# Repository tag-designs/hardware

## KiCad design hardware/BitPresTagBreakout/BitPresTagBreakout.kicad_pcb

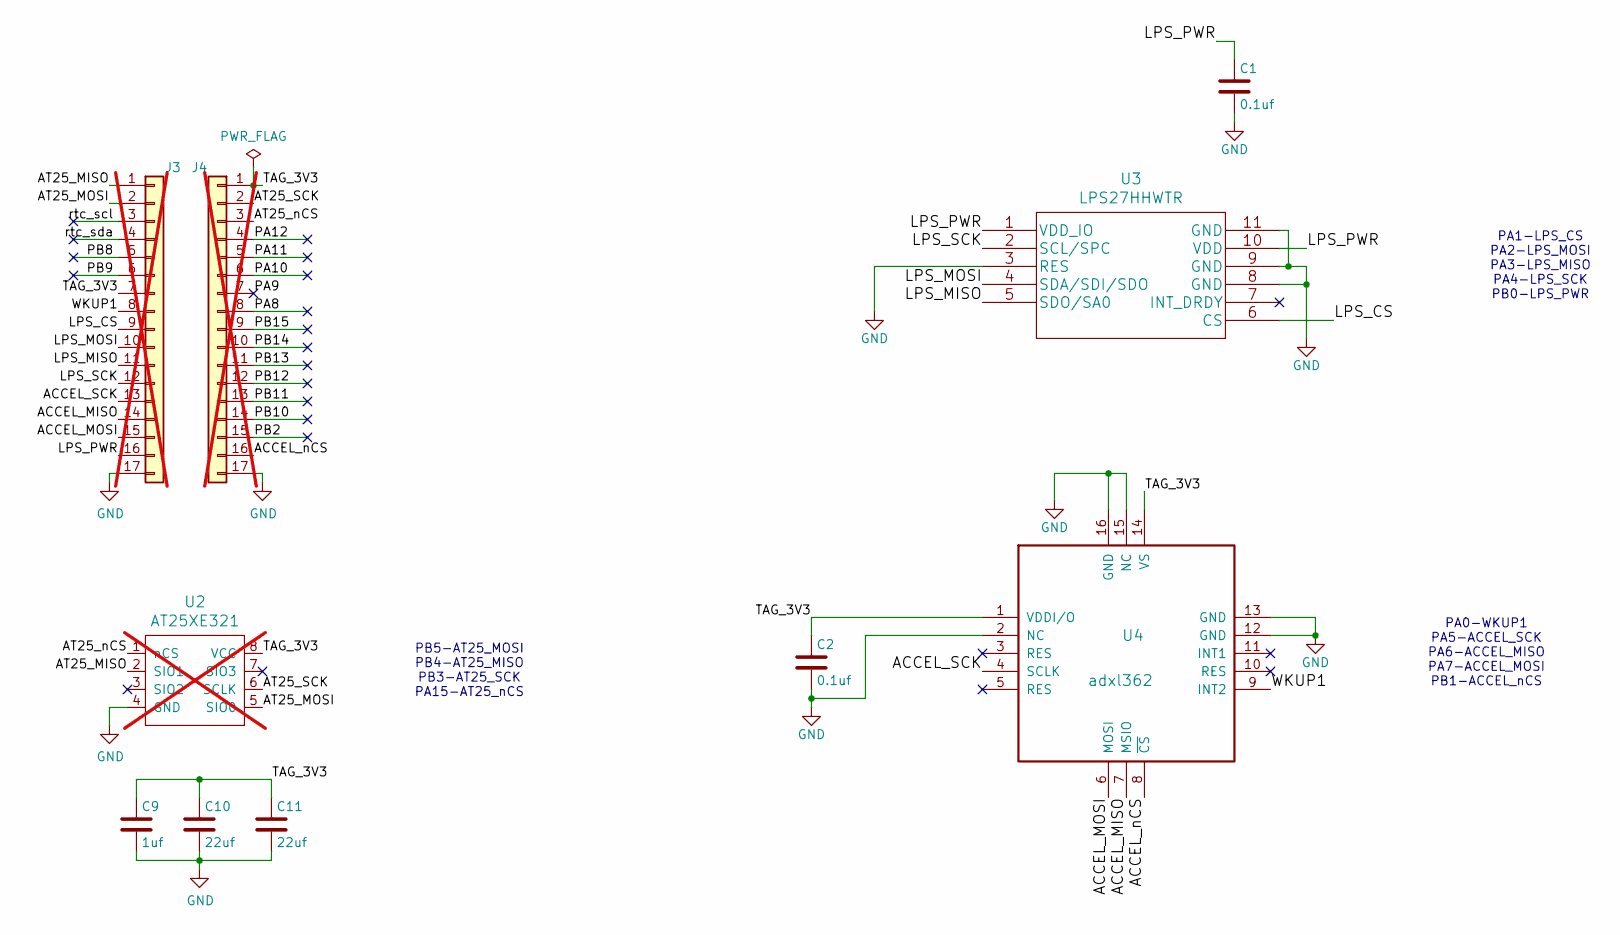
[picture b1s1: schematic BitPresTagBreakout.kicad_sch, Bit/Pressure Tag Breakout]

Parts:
C1, C2: 0.1uf; C_0201_0603Metric; MPN GRM033C81E104KE14D; LCSC C181047
C9: 1uf; C_0201_0603Metric; MPN GRM033R60J105MEA2D; LCSC C76930
C10, C11: 22uf; C_0402_1005Metric; MPN 04026D226MAT2A; LCSC C2179118
J3, J4: Conn_01x17; PinHeader_1x17_P2.54mm_Vertical_Staggered; not fitted
U2: AT25XE321; SO-8_5.3x6.2mm_P1.27mm; MPN AT25XE321D-SSHN-T; LCSC C7455379; not fitted
U3: LPS27HHWTR; MPN LPS27HHTWTR; LCSC C3253631
U4: adxl362; ADXL362; MPN ADXL362BCCZ-RL7; LCSC C192252

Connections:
/ACCEL_MISO: J3.14, U4.7 (MSIO)
/ACCEL_MOSI: J3.15, U4.6 (MOSI)
/ACCEL_SCK: J3.13, U4.4 (SCLK)
/ACCEL_nCS: J4.16, U4.8 (~CS)
/AT25_MISO: J3.1, U2.2 (SIO1)
/AT25_MOSI: J3.2, U2.5 (SIO0)
/AT25_SCK: J4.2, U2.6 (SCLK)
/AT25_nCS: J4.3, U2.1 (nCS)
/LPS_CS: J3.9, U3.6 (CS)
/LPS_MISO: J3.11, U3.5 (SDO/SA0)
/LPS_MOSI: J3.10, U3.4 (SDA/SDI/SDO)
/LPS_PWR: C1.1, J3.16, U3.1 (VDD_IO), U3.10 (VDD)
/LPS_SCK: J3.12, U3.2 (SCL/SPC)
/PA8: J4.8
/PA9: J4.7
/PA10: J4.6
/PA11: J4.5
/PA12: J4.4
/PB2: J4.15
/PB8: J3.5
/PB9: J3.6
/PB10: J4.14
/PB11: J4.13
/PB12: J4.12
/PB13: J4.11
/PB14: J4.10
/PB15: J4.9
/TAG_3V3: C2.1, C9.1, C10.1, C11.1, J3.7, J4.1, U2.8 (VCC), U4.1 (VDDI/O), U4.14 (VS)
/WKUP1: J3.8, U4.9 (INT2)
/rtc_scl: J3.3
/rtc_sda: J3.4
GND: C1.2, C2.2, C9.2, C10.2, C11.2, J3.17, J4.17, U2.4 (GND), U3.3 (RES), U3.8 (GND), U3.9 (GND), U3.11 (GND), U4.2 (NC), U4.12 (GND), U4.13 (GND), U4.15 (NC), U4.16 (GND)

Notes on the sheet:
PA0-WKUP1 PA5-ACCEL_SCK PA6-ACCEL_MISO PA7-ACCEL_MOSI PB1-ACCEL_nCS
PA1-LPS_CS PA2-LPS_MOSI PA3-LPS_MISO PA4-LPS_SCK PB0-LPS_PWR
PB5-AT25_MOSI PB4-AT25_MISO PB3-AT25_SCK PA15-AT25_nCS

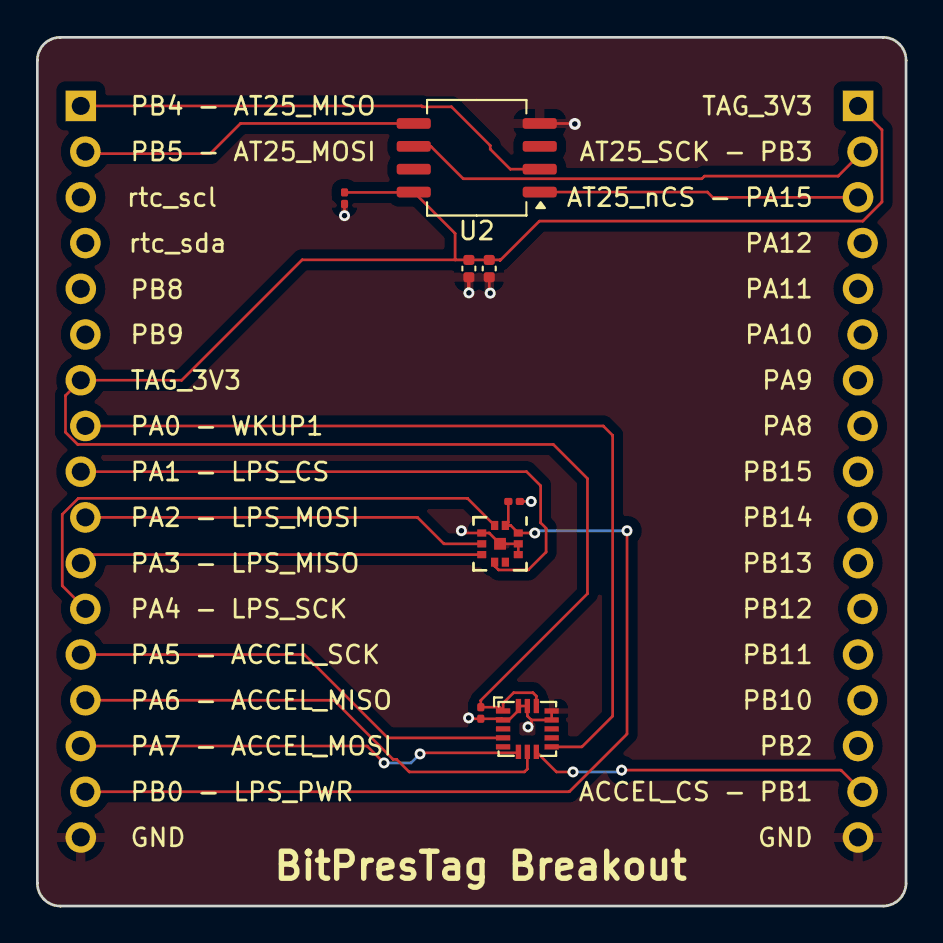
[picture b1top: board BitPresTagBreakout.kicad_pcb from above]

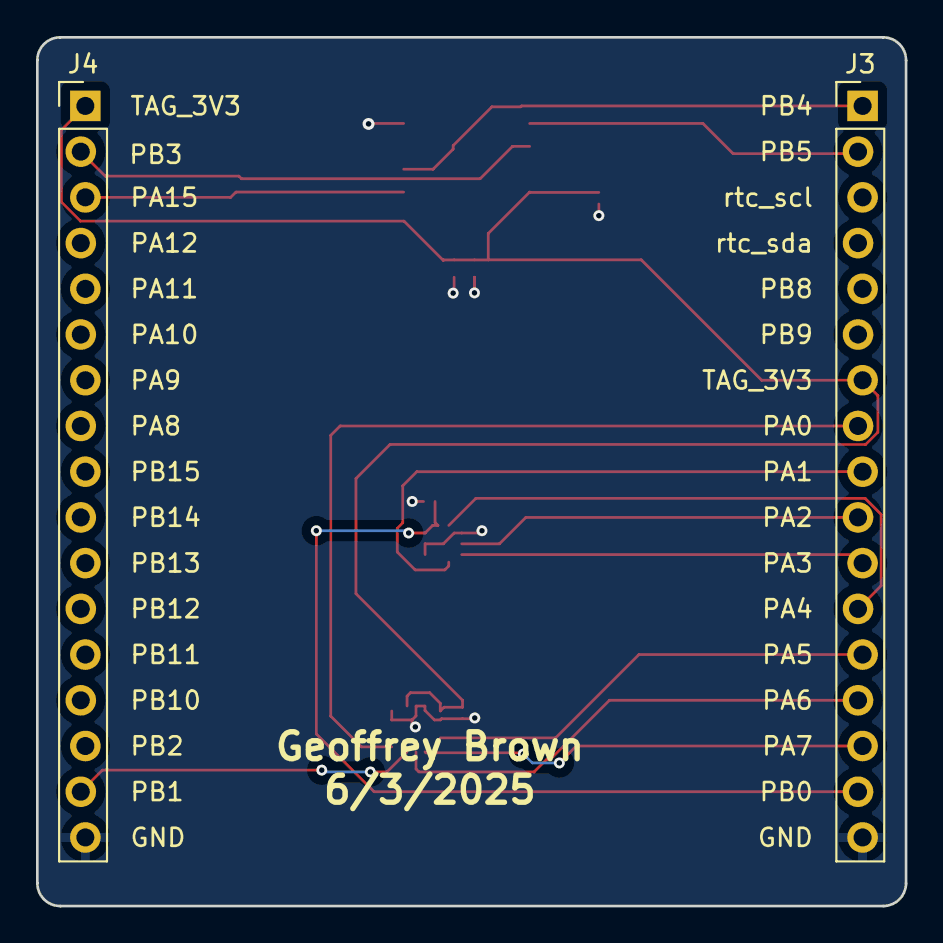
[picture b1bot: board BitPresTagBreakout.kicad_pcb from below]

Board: 2 copper layers, 48.3 x 48.3 mm, 10 parts (2 on the bottom side), 16 nets.

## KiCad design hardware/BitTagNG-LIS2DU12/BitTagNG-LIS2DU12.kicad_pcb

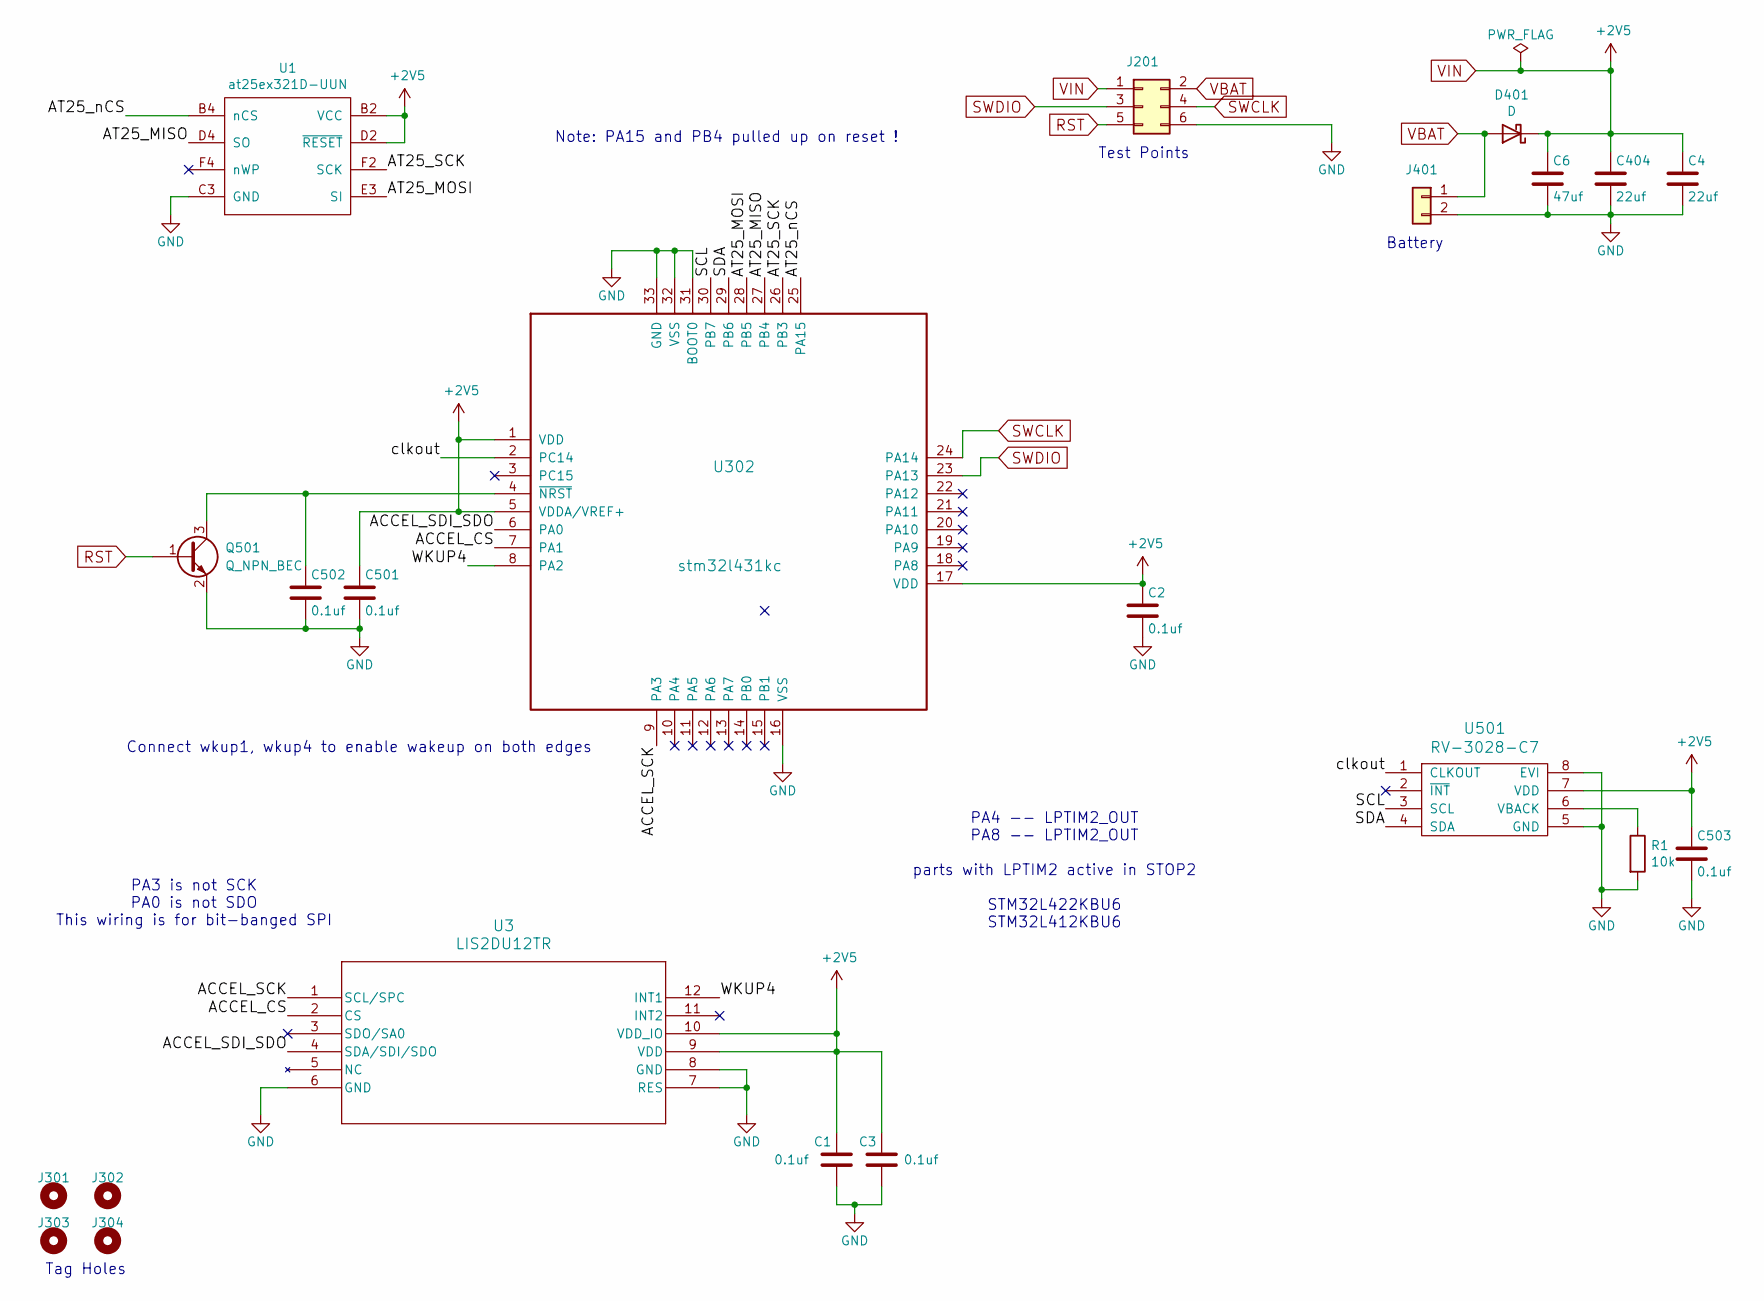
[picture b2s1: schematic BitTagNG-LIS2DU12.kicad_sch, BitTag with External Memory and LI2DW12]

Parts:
C1, C3, C501, C502, C503: 0.1uf; C_0201_0603Metric; MPN C181047; LCSC C181047
C2: 0.1uf; C_0201_0603Metric; MPN GRM033R60J105MEA2D; LCSC C76929
C4, C404: 22uf; C_0402_1005Metric; MPN 04026D226MAT2A; LCSC C2179118
C6: 47uf; C_0603_1608Metric; MPN 06036D476MAT2A
D401: D; D_0402_1005Metric; MPN CDBQC0130L-HF; LCSC C2886012
J201: CONN_02X04; tagpoints6
J301, J302, J303, J304: Conn_01x01; taghole1.1mm
J401: CONN_01X02; MS621
Q501: Q_NPN_BEC; SOT-883; MPN BC847AMB,315; LCSC C686658
R1: 10k; R_0201_0603Metric; MPN RC0201FR-0710KL; LCSC C106225
U1: at25ex321D-UUN; adesto_wlcsp12; MPN AT25FF321A-UUN-T; LCSC C1858339
U3: LIS2DU12TR; LGA-12L_LIS2DU12_STM
U302: stm32l431kc; QFN-32-1EP_5x5mm_P0.5mm_EP3.45x3.45mm; MPN STM32L432KCU6; LCSC C1337280
U501: RV-3028-C7; RV-8803-C7; MPN RV-3028-C7 32.768KHZ 1PPM-TA-QA; LCSC C3019759

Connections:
/ACCEL_CS: U3.2 (CS), U302.7 (PA1)
/ACCEL_SCK: U3.1 (SCL/SPC), U302.9 (PA3)
/ACCEL_SDI_SDO: U3.4 (SDA/SDI/SDO), U302.6 (PA0)
/AT25_MISO: U1.D4 (SO), U302.27 (PB4)
/AT25_MOSI: U1.E3 (SI), U302.28 (PB5)
/AT25_SCK: U1.F2 (SCK), U302.26 (PB3)
/AT25_nCS: U1.B4 (nCS), U302.25 (PA15)
/SCL: U302.30 (PB7), U501.3 (SCL)
/SDA: U302.29 (PB6), U501.4 (SDA)
/WKUP4: U3.12 (INT1), U302.8 (PA2)
/clkout: U302.2 (PC14), U501.1 (CLKOUT)
GND: C1.2, C2.2, C3.2, C4.2, C6.2, C404.2, C501.2, C502.2, C503.2, J201.6, J401.2, Q501.2 (E), R1.2, U1.C3 (GND), U3.6 (GND), U3.7 (RES), U3.8 (GND), U302.16 (VSS), U302.31 (BOOT0), U302.32 (VSS), U302.33 (GND), U501.5 (GND), U501.8 (EVI)
unnamed: C502.1, Q501.3 (C), U302.4 (~NRST)
unnamed: R1.1, U501.6 (VBACK)
RST: J201.5, Q501.1 (B)
SWCLK: J201.4, U302.24 (PA14)
SWDIO: J201.3, U302.23 (PA13)
VBAT: D401.2 (A), J201.2, J401.1
VIN: C1.1, C2.1, C3.1, C4.1, C6.1, C404.1, C501.1, C503.1, D401.1 (K), J201.1, U1.B2 (VCC), U1.D2 (~RESET), U3.9 (VDD), U3.10 (VDD_IO), U302.1 (VDD), U302.5 (VDDA/VREF+), U302.17 (VDD), U501.7 (VDD)

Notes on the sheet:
PA3 is not SCK PA0 is not SDO This wiring is for bit-banged SPI
Note: PA15 and PB4 pulled up on reset !
Tag Holes
Test Points
Battery
Connect wkup1, wkup4 to enable wakeup on both edges
PA4 -- LPTIM2_OUT PA8 -- LPTIM2_OUT parts with LPTIM2 active in STOP2 STM32L422KBU6 STM32L412KBU6

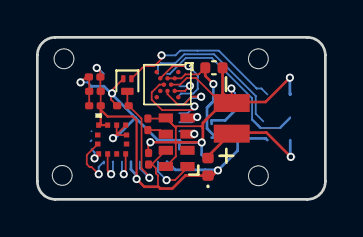
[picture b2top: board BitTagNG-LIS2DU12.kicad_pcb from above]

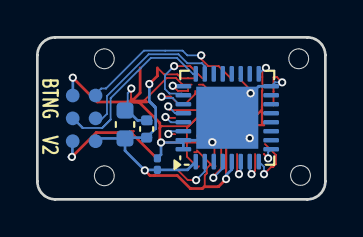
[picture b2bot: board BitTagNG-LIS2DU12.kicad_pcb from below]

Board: 2 copper layers, 16.0 x 9.0 mm, 22 parts (5 on the bottom side), 19 nets.

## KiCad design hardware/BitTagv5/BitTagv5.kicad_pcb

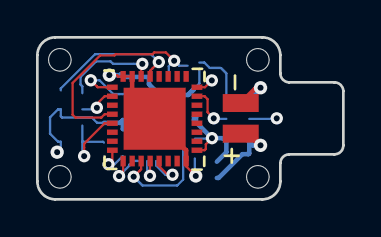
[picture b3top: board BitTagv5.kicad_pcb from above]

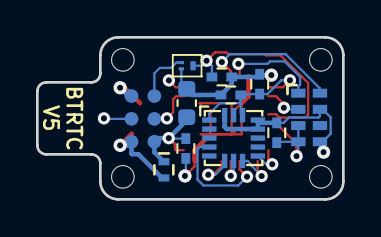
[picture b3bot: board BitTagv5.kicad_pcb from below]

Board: 4 copper layers, 17.0 x 9.0 mm, 17 parts (11 on the bottom side), 15 nets.

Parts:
C402, C403, C501, C502: 0.1uf; C_0402
C404: 4.7uf; C_0603_1608Metric
C503: 10nF; C_0402
D401: D; D_0402
J201: CONN_02X04; tagpoints6
J301, J302, J303, J304: Conn_01x01; taghole1.25mm
J401: CONN_01X02; MS621
Q501: Q_NPN_BEC; SOT883
U302: stm32l432; stm32l4
U405: adxl362; ADXL362
U501: RV-8803-C7

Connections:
/SCL: U302.29, U501.8
/SDA: U302.30, U501.1
/clkout: U302.2, U501.2
ACCEL_CS: U302.9, U405.8
GND: C402.2, C403.2, C404.2, C501.2, C502.2, C503.2, J201.6, J401.2, Q501.2, U302.16, U302.31, U302.32, U302.33, U405.12, U405.13, U405.16, U501.5, U501.7
unnamed: C502.1, Q501.3, U302.4
RST: J201.5, Q501.1
SENS_MISO: U302.12, U405.7
SENS_MOSI: U302.13, U405.6
SENS_SCLK: U302.11, U405.4
SWCLK: J201.4, U302.24
SWDIO: J201.3, U302.23
VBAT: D401.2, J201.2, J401.1
VIN: C402.1, C403.1, C404.1, C501.1, C503.1, D401.1, J201.1, U302.1, U302.5, U302.17, U405.1, U405.14, U501.3, U501.4
WKUP4: U302.8, U405.9

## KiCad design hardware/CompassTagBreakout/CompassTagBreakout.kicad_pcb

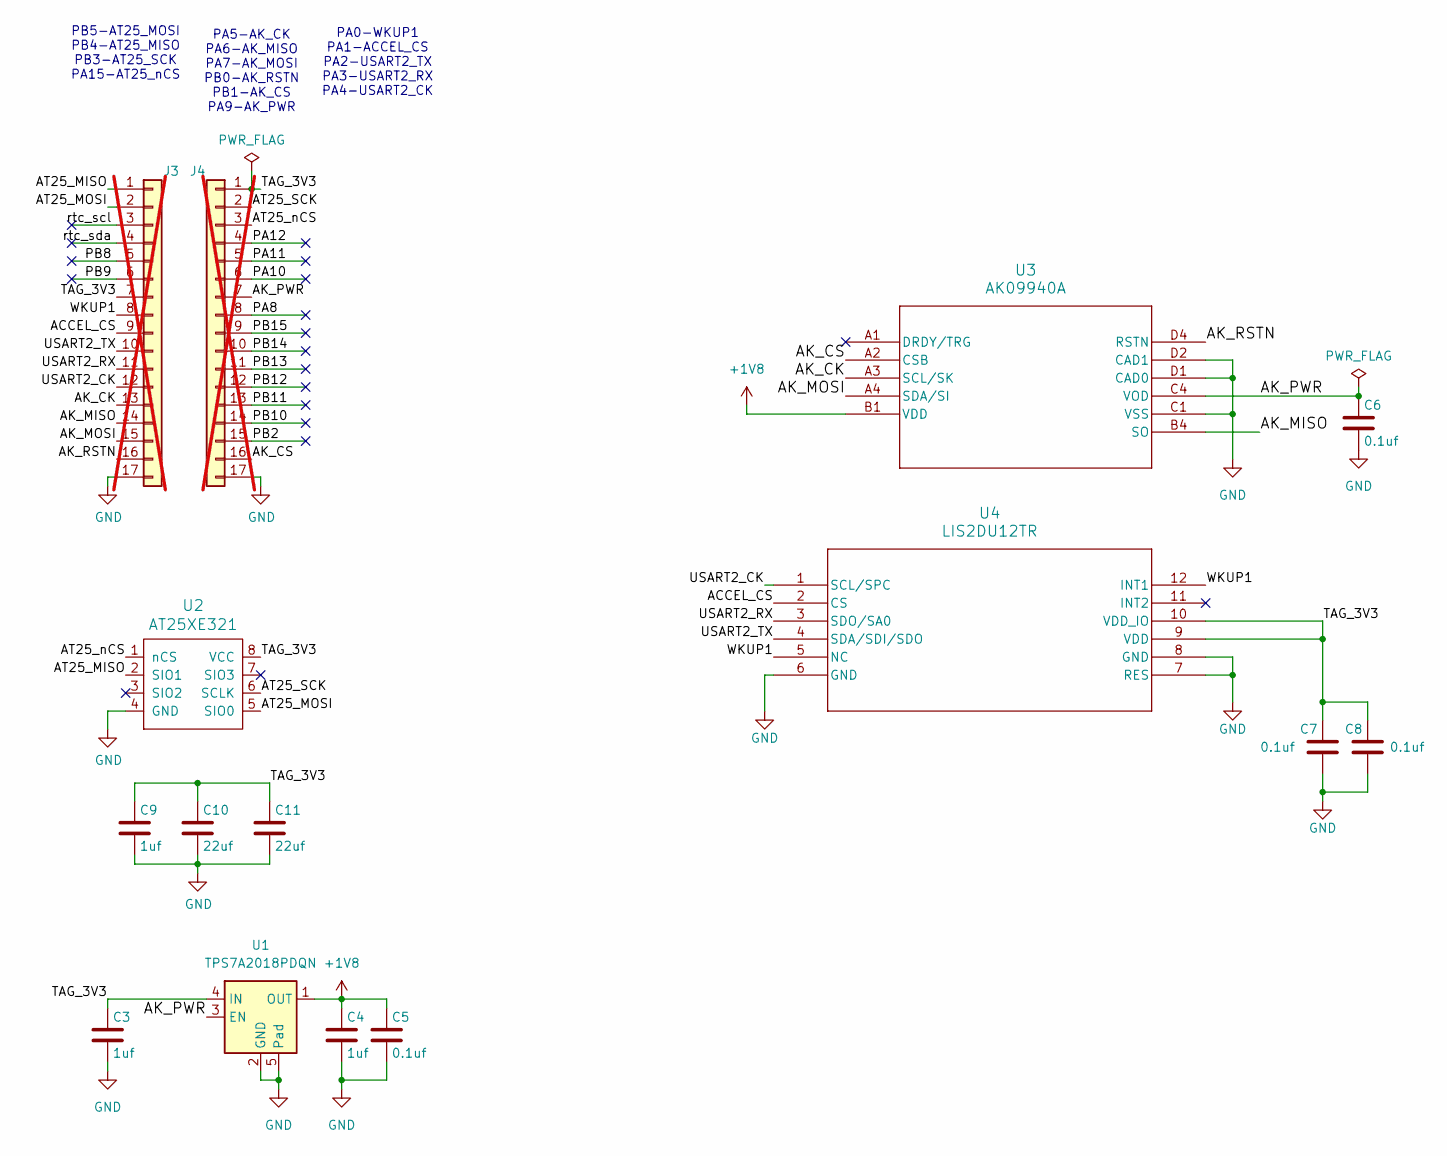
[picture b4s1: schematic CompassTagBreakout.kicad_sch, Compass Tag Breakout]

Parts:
C3, C4, C9: 1uf; C_0201_0603Metric; MPN GRM033R60J105MEA2D; LCSC C76930
C5, C6, C7, C8: 0.1uf; C_0201_0603Metric; MPN GRM033C81E104KE14D; LCSC C181047
C10, C11: 22uf; C_0402_1005Metric; MPN 04026D226MAT2A; LCSC C2179118
J3, J4: Conn_01x17; PinHeader_1x17_P2.54mm_Vertical_Staggered; not fitted
U1: TPS7A2018PDQN; Texas_X2SON-4_1x1mm_P0.65mm; MPN TPS7A2018PDQNR; LCSC C2878130
U2: AT25XE321; SO-8_5.3x6.2mm_P1.27mm; MPN AT25XE321D-SSHN-T; LCSC C7455379
U3: AK09940A; AK09940a; MPN AK09940A; LCSC C6794828
U4: LIS2DU12TR; LGA-12L_LIS2DU12_STM; MPN LIS2DU12TR; LCSC C5267411

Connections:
+1V8: C4.1, C5.1, U1.1 (OUT), U3.B1 (VDD)
/ACCEL_CS: J3.9, U4.2 (CS)
/AK_CK: J3.13, U3.A3 (SCL/SK)
/AK_CS: J4.16, U3.A2 (CSB)
/AK_MISO: J3.14, U3.B4 (SO)
/AK_MOSI: J3.15, U3.A4 (SDA/SI)
/AK_PWR: C6.1, J4.7, U1.3 (EN), U3.C4 (VOD)
/AK_RSTN: J3.16, U3.D4 (RSTN)
/AT25_MISO: J3.1, U2.2 (SIO1)
/AT25_MOSI: J3.2, U2.5 (SIO0)
/AT25_SCK: J4.2, U2.6 (SCLK)
/AT25_nCS: J4.3, U2.1 (nCS)
/PA8: J4.8
/PA10: J4.6
/PA11: J4.5
/PA12: J4.4
/PB2: J4.15
/PB8: J3.5
/PB9: J3.6
/PB10: J4.14
/PB11: J4.13
/PB12: J4.12
/PB13: J4.11
/PB14: J4.10
/PB15: J4.9
/TAG_3V3: C3.1, C7.1, C8.1, C9.1, C10.1, C11.1, J3.7, J4.1, U1.4 (IN), U2.8 (VCC), U4.9 (VDD), U4.10 (VDD_IO)
/USART2_CK: J3.12, U4.1 (SCL/SPC)
/USART2_RX: J3.11, U4.3 (SDO/SA0)
/USART2_TX: J3.10, U4.4 (SDA/SDI/SDO)
/WKUP1: J3.8, U4.5 (NC), U4.12 (INT1)
/rtc_scl: J3.3
/rtc_sda: J3.4
GND: C3.2, C4.2, C5.2, C6.2, C7.2, C8.2, C9.2, C10.2, C11.2, J3.17, J4.17, U1.2 (GND), U1.5 (Pad), U2.4 (GND), U3.C1 (VSS), U3.D1 (CAD0), U3.D2 (CAD1), U4.6 (GND), U4.7 (RES), U4.8 (GND)

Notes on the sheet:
PA5-AK_CK PA6-AK_MISO PA7-AK_MOSI PB0-AK_RSTN PB1-AK_CS PA9-AK_PWR
PA0-WKUP1 PA1-ACCEL_CS PA2-USART2_TX PA3-USART2_RX PA4-USART2_CK
PB5-AT25_MOSI PB4-AT25_MISO PB3-AT25_SCK PA15-AT25_nCS

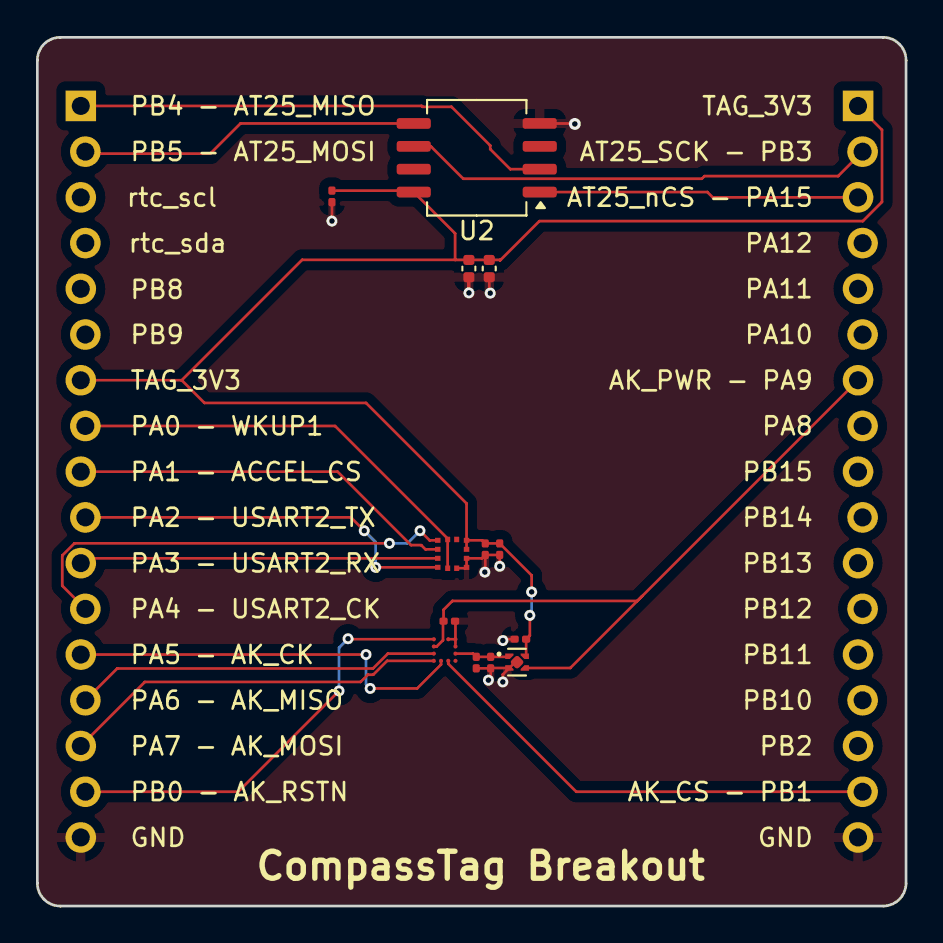
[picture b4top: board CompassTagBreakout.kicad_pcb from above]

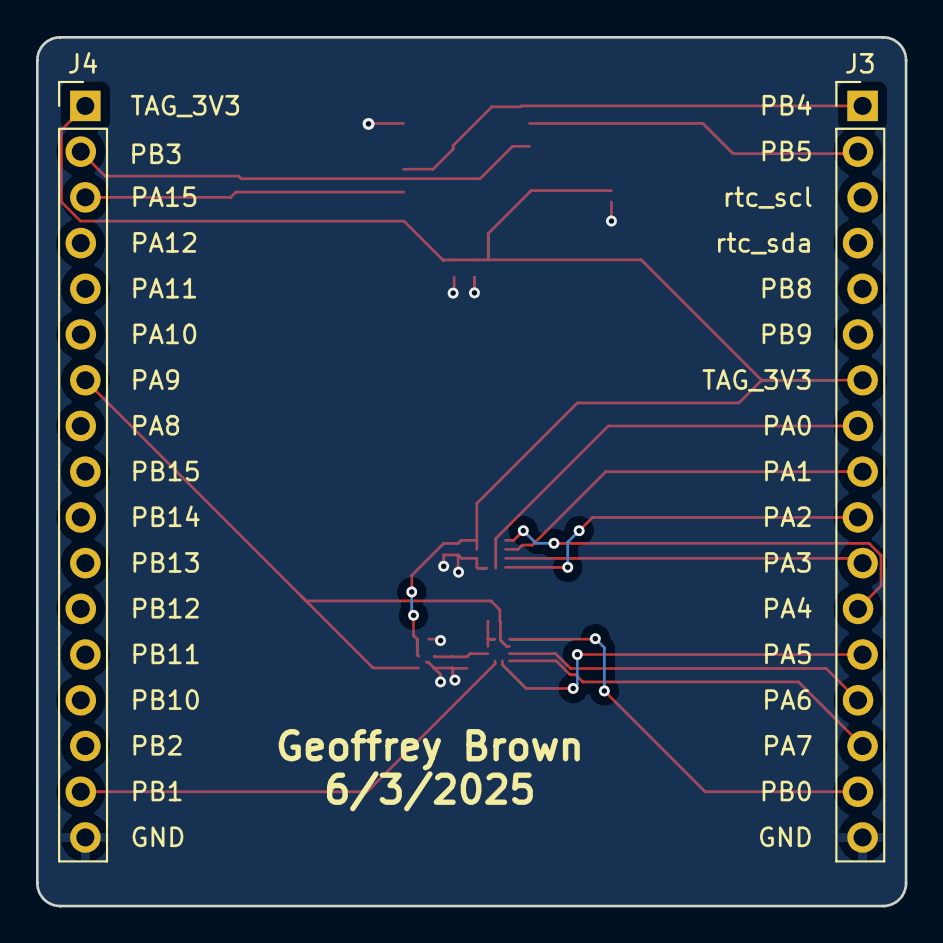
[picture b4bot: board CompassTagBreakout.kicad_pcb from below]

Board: 2 copper layers, 48.3 x 48.3 mm, 15 parts (2 on the bottom side), 18 nets.

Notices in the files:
parts and their libraries:
Copyright 2016 Accelerated Designs. All rights reserved.
